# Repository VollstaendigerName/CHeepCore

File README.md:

# CHeepCore

A minimalist, ultra-low-cost RISC-V development board based on the CH32V003 series. Designed for embedded hobbyists, students, and low-cost prototyping.

---

## Project Information

- **Name:** CHeepCore  
- **Revision:** 0.0.1b  
- **Date:** 2025-08-06  
- **KiCad Version:** 9.0.3  
- **Target Audience:** Embedded hobbyists, students, low-cost prototyping  
- **Cost Goal:** Complete microcontroller board for under 0.50€  

---

## Key Features

- CH32V003F4U6 32-bit RISC-V microcontroller (20-pin QFN)  
- 16 GPIOs exposed on 2.54 mm headers (PC0–PC7, PD0–PD7)  
- External 24 MHz crystal with 22 pF load capacitors  
- USB-C power input (VBUS → 3.3 V LDO)  
- Configurable solder jumpers for:  
  - USB-VBUS disconnect  
  - 3.3 V / 5 V MCU supply  
- SWD/JTAG programming connectors (3-pin & 10-pin, WCH-LinkE compatible)  
- Breadboard-compatible PCB outline (18.288 × 29.489 mm)  

---

## Power Configuration

1. **USB-C Supply**  
   VBUS (5 V) feeds on-board LDO → 3.3 V rail  

2. **External Supply**  
   - Cut the USB-disconnect jumper (bottom side) to isolate VBUS  
   - Inject external 5 V or 3.3 V via header  

3. **MCU Voltage Selection**  
   - Default: 3.3 V  
   - For 5 V operation, cut the 3.3 V jumper (bottom side) and bridge the center pad to 5 V  

---

## Programming with WCH-LinkE

- Connect **3V3** and **GND** pins  
- Connect **SWDIO/TMS** to the middle pin of the 3-pin header  
- SWCLK/TCK and reset lines available on 10-pin header for full JTAG  

---

## Mechanical Dimensions

- **Width:** 29.489 mm  
- **Height:** 18.288 mm  
- Compatible with standard 2.54 mm breadboards  

---

## GPIO Pinout

| #   | Header Pin | Default Function            | Alternate Function                 |
| --- | ---------- | --------------------------- | ---------------------------------- |
| 0   | PD0        | T1CH1N / OPN1               | SDA / UTX                          |
| 1   | PD1        | SWIO / AETR2                | T1CH3N / SCL / URX                 |
| 2   | PD2        | A3 / T1CH1 / T2CH3          | T1CH2N                             |
| 3   | PD3        | A4 / T2CH2 / AETR           | UCTS / T1CH4                       |
| 4   | PD4        | A7 / UCK / T2CH1ETR         | OPO / T1CH4ETR                     |
| 5   | PD5        | A5 / UTX                    | T2CH4 / URX                        |
| 6   | PD6        | A6 / URX                    | T2CH3 / UTX                        |
| 7   | PD7        | NRST / T2CH4                | OPP1 / UCK                         |
| 8   | PC7        | MISO / T1CH2                | T2CH2 / URTS                       |
| 9   | PC6        | MOSI / T1CH1CH3N            | UCTS / SDA                         |
| 10  | PC5        | SCK / T1ETR / T2CH1ETR      | SCL / UCK / T1CH3                  |
| 11  | PC4        | A2 / T1CH4 / MCO            | T1CH1CH2N                          |
| 12  | PC3        | T1CH3 / T1CHIN              | UCTS                               |
| 13  | PC2        | SCL / URTS / T1BKIN         | AETR / T2CH2 / T1ETR               |
| 14  | PC1        | SDA / NSS / T2CH4           | T2CH1ETR / T1BKIN / URX            |
| 15  | PC0        | T2CH3 / UTX                 | NSS / T1CH3                        |

---
## Bill of Material (BoM)

| Reference     | Qty | Unit Price (€) | Description                                     |
|---------------|:---:|---------------:|-------------------------------------------------|
| C101          |  1  |        0.0020  | YAGEO CC0603KRX7R7BB104 (100 nF, 0603)          |
| C102, C103    |  2  |        0.0016  | YAGEO CC0603JRNPO9BN220 (22 pF, 0603)           |
| C301, C302    |  2  |        0.0033  | Samsung CL10A105KB8NNNC (1 µF, 0603)            |
| J301          |  1  |        0.0300  | SHOU HAN TYPE-C 16-PIN 2MD(073)                 |
| R301, R302    |  2  |        0.0004  | VO SCR0603J5K1 (5.1 kΩ, 0603)                   |
| U101          |  1  |        0.1599  | CH32V003F4U6 (32-bit RISC-V microcontroller)     |
| U301          |  1  |        0.0047  | Megain MG6206K3B-33 (3.3 V LDO)                  |
| Y101          |  1  |        0.0323  | TOGNJING XTM32024000DT00351001 (24 MHz crystal) |

---

## Author & License

   VollständigerName  GitHub: https://github.com/VollstaendigerName

   <small><span style="color:lightgrey;">
   This work is licensed under Creative Commons Attribution-NonCommercial 4.0 International (CC BY-NC 4.0). See LICENSE.txt for details.

   This hardware specification and documentation have been prepared to the best of the author’s knowledge, but are provided without any warranty. The author accepts no liability for malfunctions, consequential damages, or any claims arising from the use of this information, the design, or the implemented hardware. Any liability is expressly excluded.
   </span></small>

## Repository Contents

```text
/
├── CHeepCore/       # KiCad schematic and PCB files
├── Images/          # Images of the 3d Model
├── production/      # Gerber export for fabrication   
├── README.md        # This file  
└── LICENSE.txt      # CC BY-NC 4.0

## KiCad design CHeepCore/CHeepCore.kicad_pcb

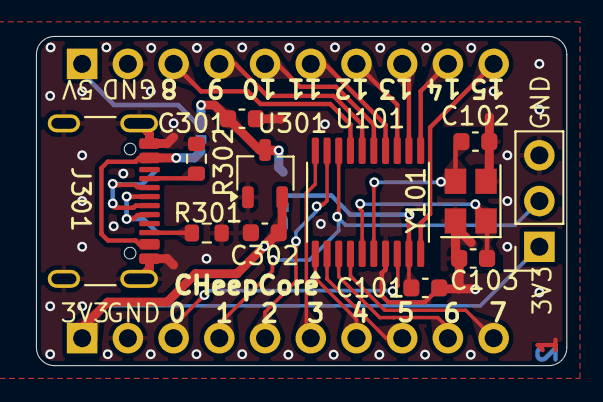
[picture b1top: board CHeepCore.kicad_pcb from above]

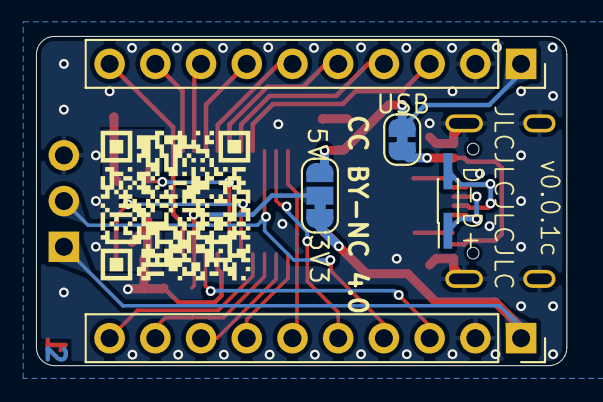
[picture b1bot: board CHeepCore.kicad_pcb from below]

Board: 2 copper layers, 29.5 x 18.3 mm, 17 parts (5 on the bottom side), 27 nets.

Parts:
C101: 100nF; C_0603_1608Metric
C102, C103: 22pF; C_0603_1608Metric
C301, C302: 1µF; C_0603_1608Metric
J101, J102: Conn_01x10; PinSocket_1x10_P2.54mm_Vertical
J103: USB; PinHeader_2x01_P1.00mm_Vertical_SMD
J201: Conn_01x03; PinSocket_1x03_P2.54mm_Vertical
J301: USB_C_Receptacle_USB2.0_16P; USB_C_Receptacle_GCT_USB4105-xx-A_16P_TopMnt_Horizontal
JP101: 3V3 or 5V; SolderJumper-3_P1.3mm_Bridged12_RoundedPad1.0x1.5mm_NumberL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
JP301: USB Disconnect; SolderJumper-2_P1.3mm_Bridged_RoundedPad1.0x1.5mm
R301, R302: 5k1; R_0603_1608Metric
U101: CH32V003FxPx; TSSOP-20_4.4x6.5mm_P0.65mm
U301: 3V3 LDO; TSOT-23
Y101: Crystal_GND24; Crystal_SMD_3225-4Pin_3.2x2.5mm

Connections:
+3V3: C302.1, J102.1, J201.1, JP101.1 (A), U301.2 (VO)
+5V: C301.1, J101.1, JP101.3 (B), JP301.2 (B), U301.3 (VI)
/PC0: J101.10, U101.10 (PC0)
/PC1: J101.9, U101.11 (PC1)
/PC2: J101.8, U101.12 (PC2)
/PC3: J101.7, U101.13 (PC3)
/PC4: J101.6, U101.14 (PC4)
/PC5: J101.5, U101.15 (PC5)
/PC6: J101.4, U101.16 (PC6)
/PC7: J101.3, U101.17 (PC7)
/PD0: J102.3, U101.8 (PD0)
/PD1: J102.4, J201.2, U101.18 (PD1)
/PD2: J102.5, U101.19 (PD2)
/PD3: J102.6, U101.20 (PD3)
/PD4: J102.7, U101.1 (PD4)
/PD5: J102.8, U101.2 (PD5)
/PD6: J102.9, U101.3 (PD6)
/PD7: J102.10, U101.4 (PD7)
/USB with LDO/D+: J103.1, J301.A6 (D+), J301.B6 (D+)
/USB with LDO/D-: J103.2, J301.A7 (D-), J301.B7 (D-)
GND: C101.2, C102.2, C103.2, C301.2, C302.2, J101.2, J102.2, J201.3, J301.A1 (GND), J301.A12 (GND), J301.B1 (GND), J301.B12 (GND), J301.S1 (SHIELD), R301.2, R302.2, U101.7 (VSS), U301.1 (GND), Y101.2, Y101.4
unnamed: J301.A5 (CC1), R302.1
unnamed: J301.B5 (CC2), R301.1
unnamed: C101.1, JP101.2 (C), U101.9 (VDD)
unnamed: J301.A4 (VBUS), J301.A9 (VBUS), J301.B4 (VBUS), J301.B9 (VBUS), JP301.1 (A)
unnamed: C103.1, U101.5 (PA1), Y101.1
unnamed: C102.1, U101.6 (PA2), Y101.3

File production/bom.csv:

Designator,Footprint,Quantity,Value,LCSC Part #
C101,0603,1,100nF,https://www.lcsc.com/product-detail/C108079.html?s_z=n_CC060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
"C102, C103",0603,2,22pF,https://www.lcsc.com/product-detail/C105620.html
"C301, C302",0603,2,1µF,https://www.lcsc.com/product-detail/C15849.html
"J101, J102",PinSocket_1x10_P2.54mm_Vertical,2,Conn_01x10,
J201,PinSocket_1x03_P2.54mm_Vertical,1,Conn_01x03,
J301,USB_C_Receptacle_GCT_USB4105-xx-A_16P_TopMnt_Horizontal,1,USB_C_Receptacle_USB2.0_16P,https://www.lcsc.com/product-detail/C2765186.html?s_z=n_USB%2520C
"R301, R302",0603,2,5k1,https://www.lcsc.com/product-detail/C3017721.html
U101,QFN-20-1EP_3x3mm_P0.4mm_EP1.65x1.65mm,1,CH32V003FxUx,https://www.lcsc.com/product-detail/C5299908.html?s_z=n_CH32v003
U301,TSOT-23,1,3V3 LDO,https://www.lcsc.com/product-detail/C48678136.html
Y101,Crystal_SMD_3225-4Pin_3.2x2.5mm,1,Crystal_GND24,https://www.lcsc.com/product-detail/C41383243.html?s_z=n_24Mhz

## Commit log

2025-08-07 Upload Files
2025-08-07 Changed Via size
    JLCPCB charges more for smaller vias. Therefore, vias are enlarged to save PCB costs.
2025-08-07 Changed Via size
    JLCPCB charges more for smaller vias. Therefore, vias are enlarged to save PCB costs. Now only 2€ for 5 PCBs
2025-08-07 Update README.md
    added BOM
2025-08-07 Logo Upload
    Cheep Cheep
2025-08-07 Update README.md
    Added Images to Readme
2025-08-07 Better images
    Removed background
2025-08-07 Update LICENSE.txt
    Exceptions for science and small businesses
2025-08-07 Update README.md
    CHeepCore as branch
2025-08-08 Added USB to smd pad
    USB smd pads added on the back
2025-08-08 Changed to TSSOP Footprint
    Changed to WCH CH32V003F4P6
2025-08-08 Production Files
2025-08-08 Update Production Files
    with USB pads on the back
2025-08-08 Update images
2025-08-08 TSSOP Images

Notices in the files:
CHeepCore/CHeepCore.kicad_pcb:
LICENSE: CC BY-NC 4.0. https://creativecommons.org/licenses/by-nc/4.0
